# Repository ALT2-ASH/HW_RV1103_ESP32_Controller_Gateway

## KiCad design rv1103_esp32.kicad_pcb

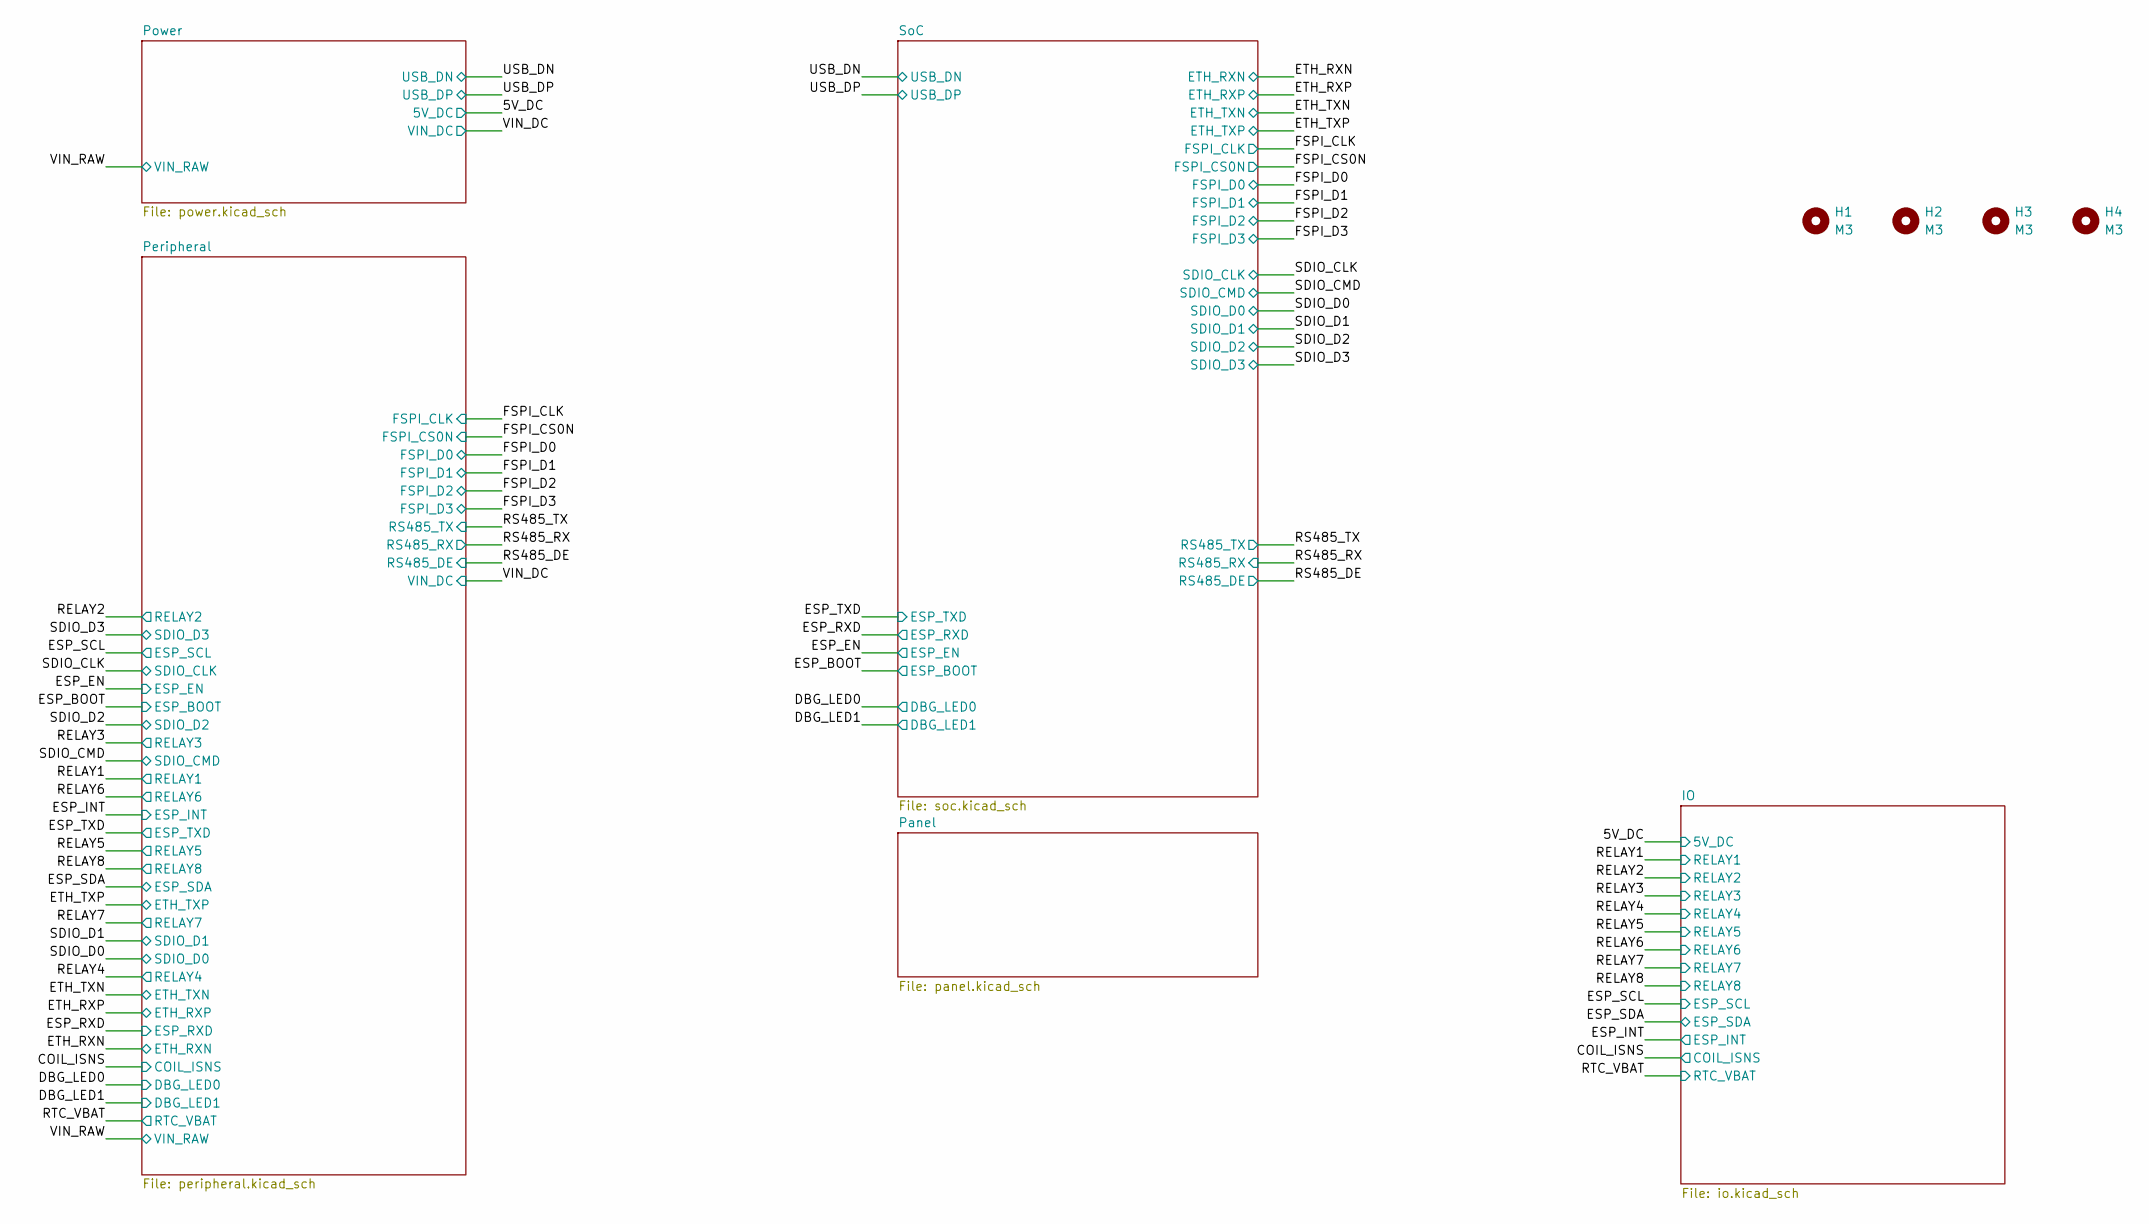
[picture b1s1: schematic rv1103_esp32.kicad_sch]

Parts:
H1, H2, H3, H4: M3; MountingHole_3.2mm_M3

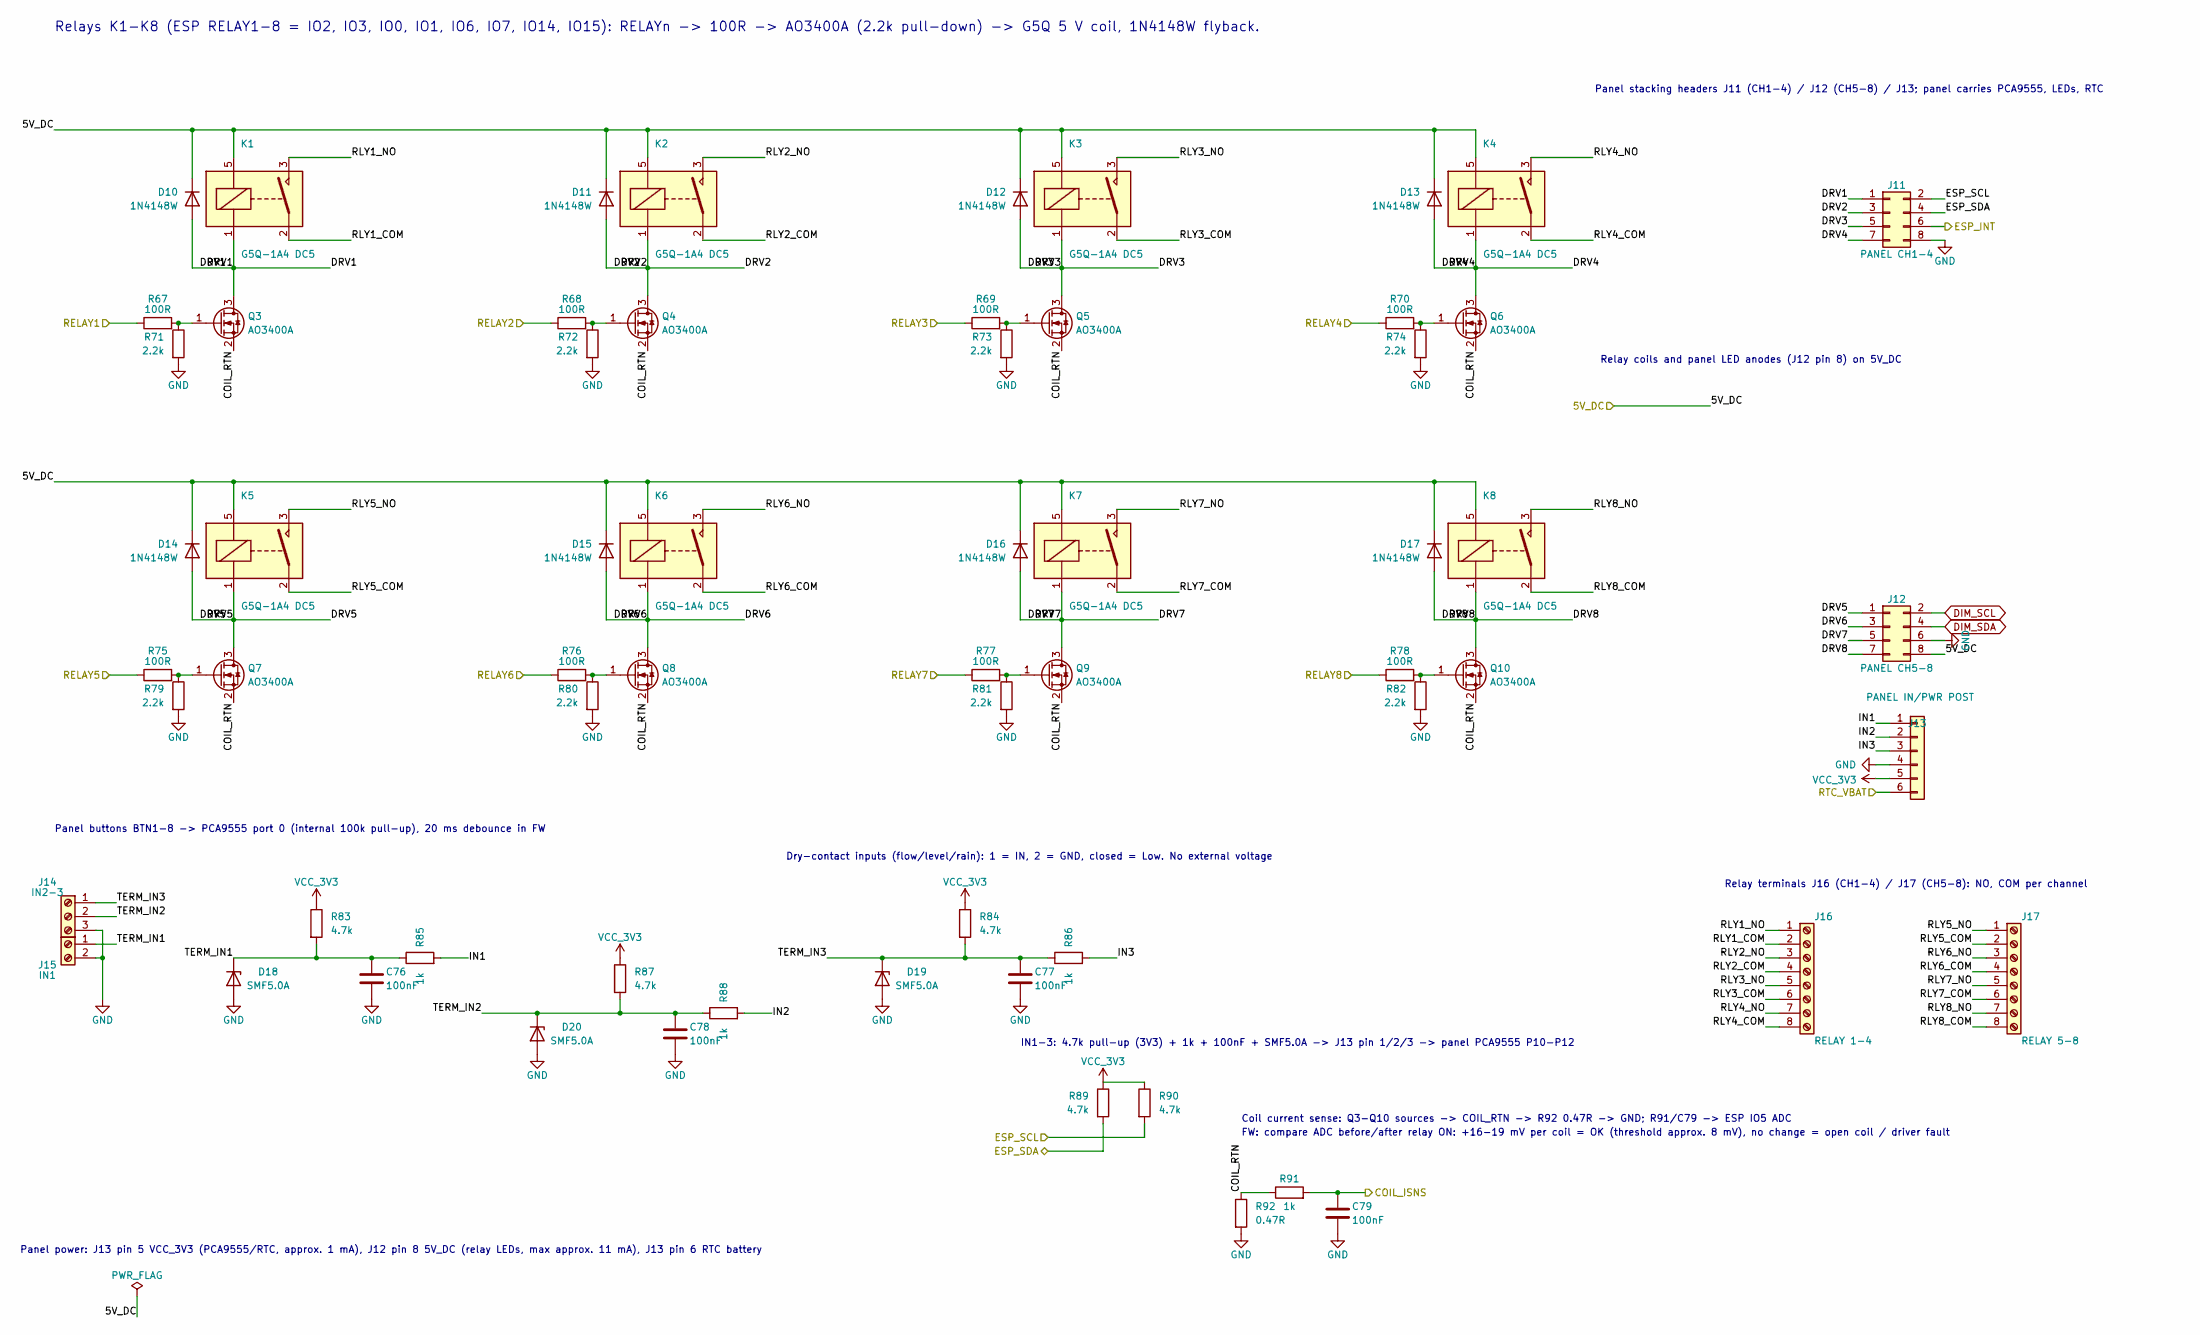
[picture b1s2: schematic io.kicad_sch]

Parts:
C76, C77, C78, C79: 100nF; C_0402_1005Metric; LCSC C1525
D10, D11, D12, D13, D14, D15, D16, D17: 1N4148W; D_SOD-123; MPN 1N4148W; LCSC C81598
D18, D19, D20: SMF5.0A; D_SOD-123F; LCSC C2759874
J11: PANEL CH1-4; PinHeader_2x04_P2.54mm_Vertical; MPN PZ254V-12-8P; LCSC C492421
J12: PANEL CH5-8; PinHeader_2x04_P2.54mm_Vertical; MPN PZ254V-12-8P; LCSC C492421
J13: PANEL IN/PWR POST; PinHeader_1x06_P2.54mm_Vertical; LCSC C492405
J14: IN2-3; TerminalBlock_DB127V-5.0_1x03_P5.00mm; MPN DB127V-5.0-3P-GN-S; LCSC C395886
J15: IN1; TerminalBlock_DB127V-5.0_1x02_P5.00mm; MPN DB127V-5.0-2P-GN-S; LCSC C395885
J16: RELAY 1-4; TerminalBlock_bornier-8_P5.08mm; MPN DB128V-5.08-8P-GN-S; LCSC C5143711
J17: RELAY 5-8; TerminalBlock_bornier-8_P5.08mm; MPN DB128V-5.08-8P-GN-S; LCSC C5143711
K1, K2, K3, K4, K5, K6, K7, K8: G5Q-1A4 DC5; Relay_SPST_Omron-G5Q-1A; MPN G5Q-1A4 DC5; LCSC_ALT C397241 G5Q-14 DC5 (SPDT 400mW coil, pa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
Q3, Q4, Q5, Q6, Q7, Q8, Q9, Q10: AO3400A; SOT-23; MPN AO3400A; LCSC C20917
R67, R68, R69, R70, R75, R76, R77, R78: 100R; R_0402_1005Metric; LCSC C25076
R71, R72, R73, R74, R79, R80, R81, R82: 2.2k; R_0402_1005Metric; LCSC C25879
R83, R84, R87, R89, R90: 4.7k; R_0402_1005Metric; LCSC C25900
R85, R86, R88, R91: 1k; R_0402_1005Metric; LCSC C11702
R92: 0.47R; R_1206_3216Metric; LCSC C327076

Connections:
/5V_DC: D10.1 (K), D11.1 (K), D12.1 (K), D13.1 (K), D14.1 (K), D15.1 (K), D16.1 (K), D17.1 (K), J12.8, K1.5, K2.5, K3.5, K4.5, K5.5, K6.5, K7.5, K8.5; also elsewhere on the board
/COIL_ISNS: C79.1, R91.2; also elsewhere on the board
/ESP_INT: J11.6; also elsewhere on the board
/ESP_SCL: J11.2, R90.2; also elsewhere on the board
/ESP_SDA: J11.4, R89.2; also elsewhere on the board
/IO/COIL_RTN: Q3.2 (S), Q4.2 (S), Q5.2 (S), Q6.2 (S), Q7.2 (S), Q8.2 (S), Q9.2 (S), Q10.2 (S), R91.1, R92.1
/IO/DRV1: D10.2 (A), J11.1, K1.1, Q3.3 (D)
/IO/DRV2: D11.2 (A), J11.3, K2.1, Q4.3 (D)
/IO/DRV3: D12.2 (A), J11.5, K3.1, Q5.3 (D)
/IO/DRV4: D13.2 (A), J11.7, K4.1, Q6.3 (D)
/IO/DRV5: D14.2 (A), J12.1, K5.1, Q7.3 (D)
/IO/DRV6: D15.2 (A), J12.3, K6.1, Q8.3 (D)
/IO/DRV7: D16.2 (A), J12.5, K7.1, Q9.3 (D)
/IO/DRV8: D17.2 (A), J12.7, K8.1, Q10.3 (D)
/IO/IN1: J13.1, R85.2
/IO/IN2: J13.2, R88.2
/IO/IN3: J13.3, R86.2
/IO/RLY1_COM: J16.2, K1.2
/IO/RLY1_NO: J16.1, K1.3
/IO/RLY2_COM: J16.4, K2.2
/IO/RLY2_NO: J16.3, K2.3
/IO/RLY3_COM: J16.6, K3.2
/IO/RLY3_NO: J16.5, K3.3
/IO/RLY4_COM: J16.8, K4.2
/IO/RLY4_NO: J16.7, K4.3
/IO/RLY5_COM: J17.2, K5.2
/IO/RLY5_NO: J17.1, K5.3
/IO/RLY6_COM: J17.4, K6.2
/IO/RLY6_NO: J17.3, K6.3
/IO/RLY7_COM: J17.6, K7.2
/IO/RLY7_NO: J17.5, K7.3
/IO/RLY8_COM: J17.8, K8.2
/IO/RLY8_NO: J17.7, K8.3
/IO/TERM_IN1: C76.1, D18.1 (K), J15.1, R83.2, R85.1
/IO/TERM_IN2: C78.1, D20.1 (K), J14.2, R87.2, R88.1
/IO/TERM_IN3: C77.1, D19.1 (K), J14.1, R84.2, R86.1
/RELAY1: R67.1; also elsewhere on the board
/RELAY2: R68.1; also elsewhere on the board
/RELAY3: R69.1; also elsewhere on the board
/RELAY4: R70.1; also elsewhere on the board
/RELAY5: R75.1; also elsewhere on the board
/RELAY6: R76.1; also elsewhere on the board
/RELAY7: R77.1; also elsewhere on the board
/RELAY8: R78.1; also elsewhere on the board
/RTC_VBAT: J13.6; also elsewhere on the board
DIM_SCL: J12.2; also elsewhere on the board
DIM_SDA: J12.4; also elsewhere on the board
GND: C76.2, C77.2, C78.2, C79.2, D18.2 (A), D19.2 (A), D20.2 (A), J11.8, J12.6, J13.4, J14.3, J15.2, R71.2, R72.2, R73.2, R74.2, R79.2, R80.2, R81.2, R82.2, R92.2; also elsewhere on the board
unnamed: Q3.1 (G), R67.2, R71.1
unnamed: Q4.1 (G), R68.2, R72.1
unnamed: Q5.1 (G), R69.2, R73.1
unnamed: Q6.1 (G), R70.2, R74.1
unnamed: Q7.1 (G), R75.2, R79.1
unnamed: Q8.1 (G), R76.2, R80.1
unnamed: Q9.1 (G), R77.2, R81.1
unnamed: Q10.1 (G), R78.2, R82.1
VCC_3V3: J13.5, R83.1, R84.1, R87.1, R89.1, R90.1; also elsewhere on the board

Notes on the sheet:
FW: compare ADC before/after relay ON: +16-19 mV per coil = OK (threshold approx. 8 mV), no change = open coil / driver fault
Relay coils and panel LED anodes (J12 pin 8) on 5V_DC
Panel stacking headers J11 (CH1-4) / J12 (CH5-8) / J13; panel carries PCA9555, LEDs, RTC
IN1-3: 4.7k pull-up (3V3) + 1k + 100nF + SMF5.0A -> J13 pin 1/2/3 -> panel PCA9555 P10-P12
Relay terminals J16 (CH1-4) / J17 (CH5-8): NO, COM per channel
Panel power: J13 pin 5 VCC_3V3 (PCA9555/RTC, approx. 1 mA), J12 pin 8 5V_DC (relay LEDs, max approx. 11 mA), J13 pin 6 RTC battery
Coil current sense: Q3-Q10 sources -> COIL_RTN -> R92 0.47R -> GND; R91/C79 -> ESP IO5 ADC
Relays K1-K8 (ESP RELAY1-8 = IO2, IO3, IO0, IO1, IO6, IO7, IO14, IO15): RELAYn -> 100R -> AO3400A (2.2k pull-down) -> G5Q 5 V coil, 1N4148W flyback.
Panel buttons BTN1-8 -> PCA9555 port 0 (internal 100k pull-up), 20 ms debounce in FW
Dry-contact inputs (flow/level/rain): 1 = IN, 2 = GND, closed = Low. No external voltage

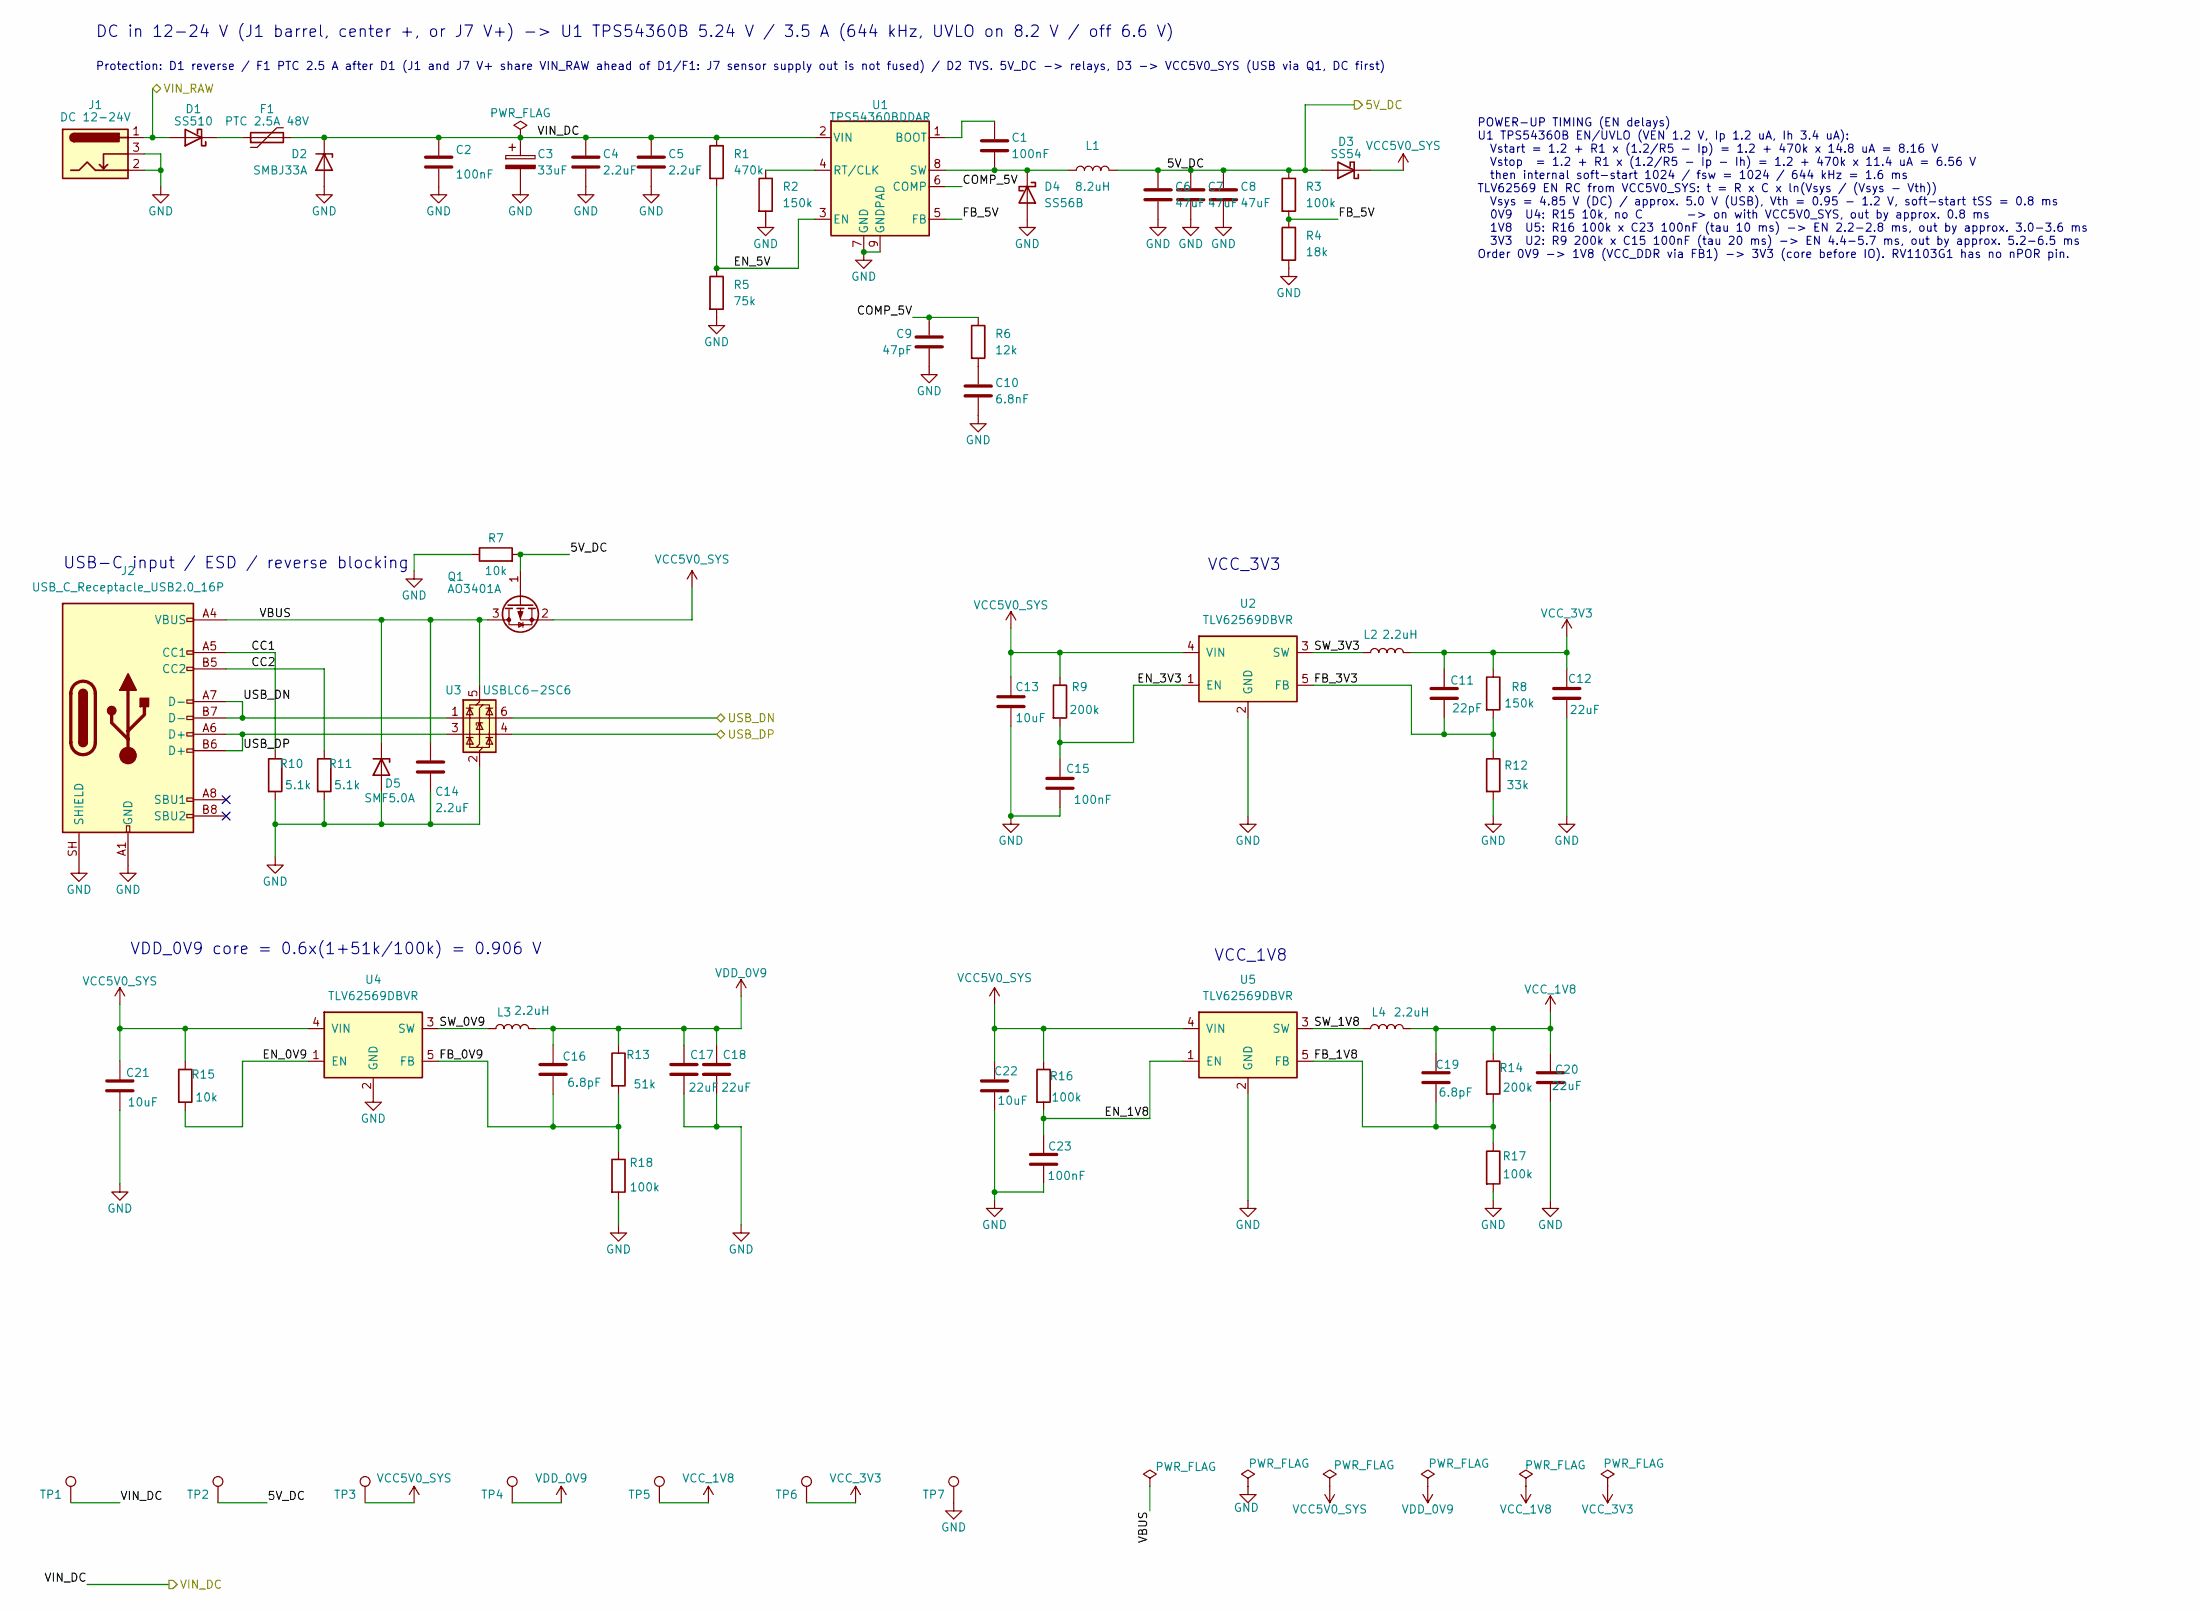
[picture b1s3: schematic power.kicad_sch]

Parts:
C1: 100nF; C_0603_1608Metric; LCSC C14663
C2: 100nF; C_0805_2012Metric; LCSC C28233
C3: 33uF; CP_Elec_6.3x7.7; Voltage 63V; MPN MV330M063E077ETR; LCSC C402500
C4, C5: 2.2uF; C_1210_3225Metric; Voltage 100V; MPN 1210B225K101NT; LCSC C42400139
C6, C7, C8: 47uF; C_1206_3216Metric; Voltage 10V; MPN CL31A476MPHNNNE; LCSC C96123
C9: 47pF; C_0402_1005Metric; MPN 0402CG470J500NT; LCSC C1567
C10: 6.8nF; C_0402_1005Metric; LCSC C1542
C11: 22pF; C_0402_1005Metric; MPN 0402CG220J500NT; LCSC C1555
C12, C17, C18, C20: 22uF; C_0603_1608Metric; LCSC C59461
C13, C21, C22: 10uF; C_0603_1608Metric; LCSC C19702
C14: 2.2uF; C_0603_1608Metric; LCSC C23630
C15, C23: 100nF; C_0402_1005Metric; LCSC C1525
C16, C19: 6.8pF; C_0402_1005Metric; LCSC C1576
D1: SS510; D_SMA; MPN SS510; LCSC C65010
D2: SMBJ33A; D_SMB; MPN SMBJ33A; LCSC C78419
D3: SS54; D_SMA; MPN SS54; LCSC C22452
D4: SS56B; D_SMB; MPN SS56B; LCSC C18199180
D5: SMF5.0A; D_SOD-123F; LCSC C2759874
F1: PTC 2.5A 48V; Fuse_2920_7451Metric; MPN 2920L250/48GR; LCSC C49326264
J1: DC 12-24V; DC-005-A200_XUNPU_Horizontal; MPN DC-005-A200; LCSC C720557
J2: USB_C_Receptacle_USB2.0_16P; USB_C_Receptacle_HRO_TYPE-C-31-D-06_Vertical; MPN TYPE-C-31-D-06A; LCSC C22464422
L1: 8.2uH; L_Sunlord_SWPA8065S; MPN FNR8065S8R2MT; LCSC C168161
L2, L3, L4: 2.2uH; L_Sunlord_SWPA4030S; MPN SWPA4030S2R2NT; LCSC C279948
Q1: AO3401A; SOT-23; MPN AO3401A; LCSC C15127
R1: 470k; R_0402_1005Metric; Tolerance 1%; MPN 0402WGF4703TCE; LCSC C25790
R2, R8: 150k; R_0402_1005Metric; Tolerance 1%; MPN 0402WGF1503TCE; LCSC C25755
R3: 100k; R_0402_1005Metric; Tolerance 1%; MPN 0402WGF1003TCE; LCSC C25741
R4: 18k; R_0402_1005Metric; Tolerance 1%; MPN 0402WGF1802TCE; LCSC C25762
R5: 75k; R_0402_1005Metric; Tolerance 1%; MPN 0402WGF7502TCE; LCSC C25798
R6: 12k; R_0402_1005Metric; Tolerance 1%; MPN 0402WGF1202TCE; LCSC C25752
R7, R15: 10k; R_0402_1005Metric; LCSC C25744
R9: 200k; R_0402_1005Metric; LCSC C25764
R10, R11: 5.1k; R_0402_1005Metric; LCSC C25905
R12: 33k; R_0402_1005Metric; Tolerance 1%; MPN 0402WGF3302TCE; LCSC C25779
R13: 51k; R_0402_1005Metric; Tolerance 1%; MPN 0402WGF5102TCE; LCSC C25794
R14: 200k; R_0402_1005Metric; Tolerance 1%; LCSC C25764
R16: 100k; R_0402_1005Metric; LCSC C25741
R17, R18: 100k; R_0402_1005Metric; Tolerance 1%; LCSC C25741
TP1: VIN_DC; TestPoint_Pad_D1.5mm
TP2: 5V_DC; TestPoint_Pad_D1.5mm
TP3: VCC5V0_SYS; TestPoint_Pad_D1.5mm
TP4: VDD_0V9; TestPoint_Pad_D1.5mm
TP5: VCC_1V8; TestPoint_Pad_D1.5mm
TP6: VCC_3V3; TestPoint_Pad_D1.5mm
TP7: GND; TestPoint_Pad_D1.5mm
U1: TPS54360BDDAR; TI_SO-PowerPAD-8_ThermalVias; MPN TPS54360BDDAR; LCSC C524806
U2, U4, U5: TLV62569DBVR; SOT-23-5_TI_DBV0005A; MPN TLV62569DBVR; LCSC C141836
U3: USBLC6-2SC6; SOT-23-6; LCSC C7519

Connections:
/5V_DC: C6.1, C7.1, C8.1, D3.2 (A), L1.2, Q1.1 (G), R3.1, R7.2, TP2.1 (1_1); also elsewhere on the board
/Power/CC1: J2.A5 (CC1), R10.1
/Power/CC2: J2.B5 (CC2), R11.1
/Power/COMP_5V: C9.1, R6.1, U1.6 (COMP)
/Power/EN_0V9: R15.2, U4.1 (EN)
/Power/EN_1V8: C23.1, R16.2, U5.1 (EN)
/Power/EN_3V3: C15.1, R9.2, U2.1 (EN)
/Power/EN_5V: R1.2, R5.1, U1.3 (EN)
/Power/FB_0V9: C16.2, R13.2, R18.1, U4.5 (FB)
/Power/FB_1V8: C19.2, R14.2, R17.1, U5.5 (FB)
/Power/FB_3V3: C11.2, R8.2, R12.1, U2.5 (FB)
/Power/FB_5V: R3.2, R4.1, U1.5 (FB)
/Power/SW_0V9: L3.1, U4.3 (SW)
/Power/SW_1V8: L4.1, U5.3 (SW)
/Power/SW_3V3: L2.1, U2.3 (SW)
/Power/VBUS: C14.1, D5.1 (K), J2.A4 (VBUS), J2.A9 (VBUS), J2.B4 (VBUS), J2.B9 (VBUS), Q1.3 (D), U3.5 (VBUS)
/USB_DN: J2.A7 (D-), J2.B7 (D-), U3.1 (I/O1), U3.6 (I/O1); also elsewhere on the board
/USB_DP: J2.A6 (D+), J2.B6 (D+), U3.3 (I/O2), U3.4 (I/O2); also elsewhere on the board
/VIN_DC: C2.1, C3.1, C4.1, C5.1, D2.1 (K), F1.2, R1.1, TP1.1 (1_1), U1.2 (VIN); also elsewhere on the board
/VIN_RAW: D1.2 (A), J1.1; also elsewhere on the board
GND: C2.2, C3.2, C4.2, C5.2, C6.2, C7.2, C8.2, C9.2, C10.2, C12.2, C13.2, C14.2, C15.2, C17.2, C18.2, C20.2, C21.2, C22.2, C23.2, D2.2 (A), D4.2 (A), D5.2 (A), J1.2, J1.3, J2.A1 (GND), J2.A12 (GND), J2.B1 (GND), J2.B12 (GND), J2.SH (SHIELD), R2.2, R4.2, R5.2, R7.1, R10.2, R11.2, R12.2, R17.2, R18.2, TP7.1 (1_1), U1.7 (GND), U1.9 (GNDPAD), U2.2 (GND), U3.2 (GND), U4.2 (GND), U5.2 (GND); also elsewhere on the board
unnamed: C10.1, R6.2
unnamed: D1.1 (K), F1.1
unnamed: C1.2, D4.1 (K), L1.1, U1.8 (SW)
unnamed: C1.1, U1.1 (BOOT)
unnamed: R2.1, U1.4 (RT/CLK)
VCC5V0_SYS: C13.1, C21.1, C22.1, D3.1 (K), Q1.2 (S), R9.1, R15.1, R16.1, TP3.1 (1_1), U2.4 (VIN), U4.4 (VIN), U5.4 (VIN)
VCC_1V8: C19.1, C20.1, L4.2, R14.1, TP5.1 (1_1); also elsewhere on the board
VCC_3V3: C11.1, C12.1, L2.2, R8.1, TP6.1 (1_1); also elsewhere on the board
VDD_0V9: C16.1, C17.1, C18.1, L3.2, R13.1, TP4.1 (1_1); also elsewhere on the board

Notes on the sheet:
VCC_3V3
DC in 12-24 V (J1 barrel, center +, or J7 V+) -> U1 TPS54360B 5.24 V / 3.5 A (644 kHz, UVLO on 8.2 V / off 6.6 V)
POWER-UP TIMING (EN delays) U1 TPS54360B EN/UVLO (VEN 1.2 V, Ip 1.2 uA, Ih 3.4 uA): Vstart = 1.2 + R1 x (1.2/R5 - Ip) = 1.2 + 470k x 14.8 uA = 8.16 V Vstop = 1.2 + R1 x (1.2/R5 - Ip - Ih) = 1.2 + 470k x 11.4 uA = 6.56 V then internal soft-start 1024 / fsw = 1024 / 644 kHz = 1.6 ms TLV62569 EN RC fr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
VDD_0V9 core = 0.6x(1+51k/100k) = 0.906 V
Protection: D1 reverse / F1 PTC 2.5 A after D1 (J1 and J7 V+ share VIN_RAW ahead of D1/F1: J7 sensor supply out is not fused) / D2 TVS. 5V_DC -> relays, D3 -> VCC5V0_SYS (USB via Q1, DC first)
VCC_1V8
USB-C input / ESD / reverse blocking

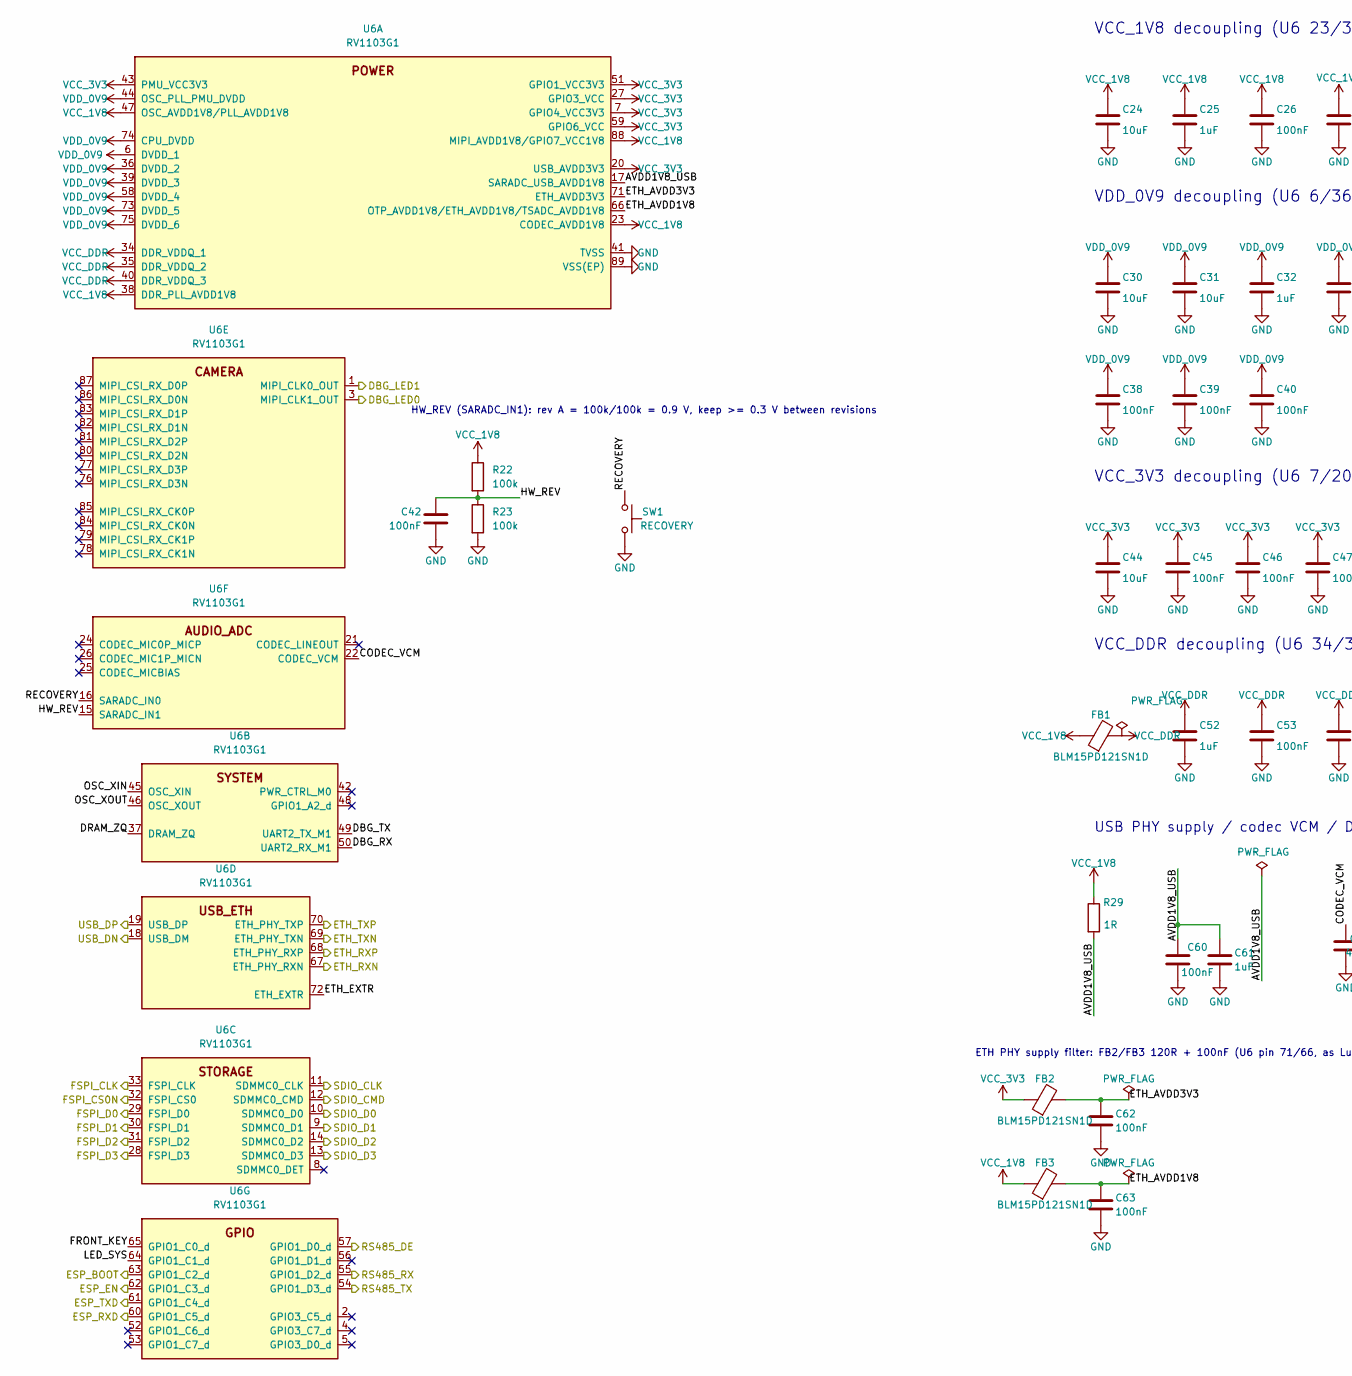
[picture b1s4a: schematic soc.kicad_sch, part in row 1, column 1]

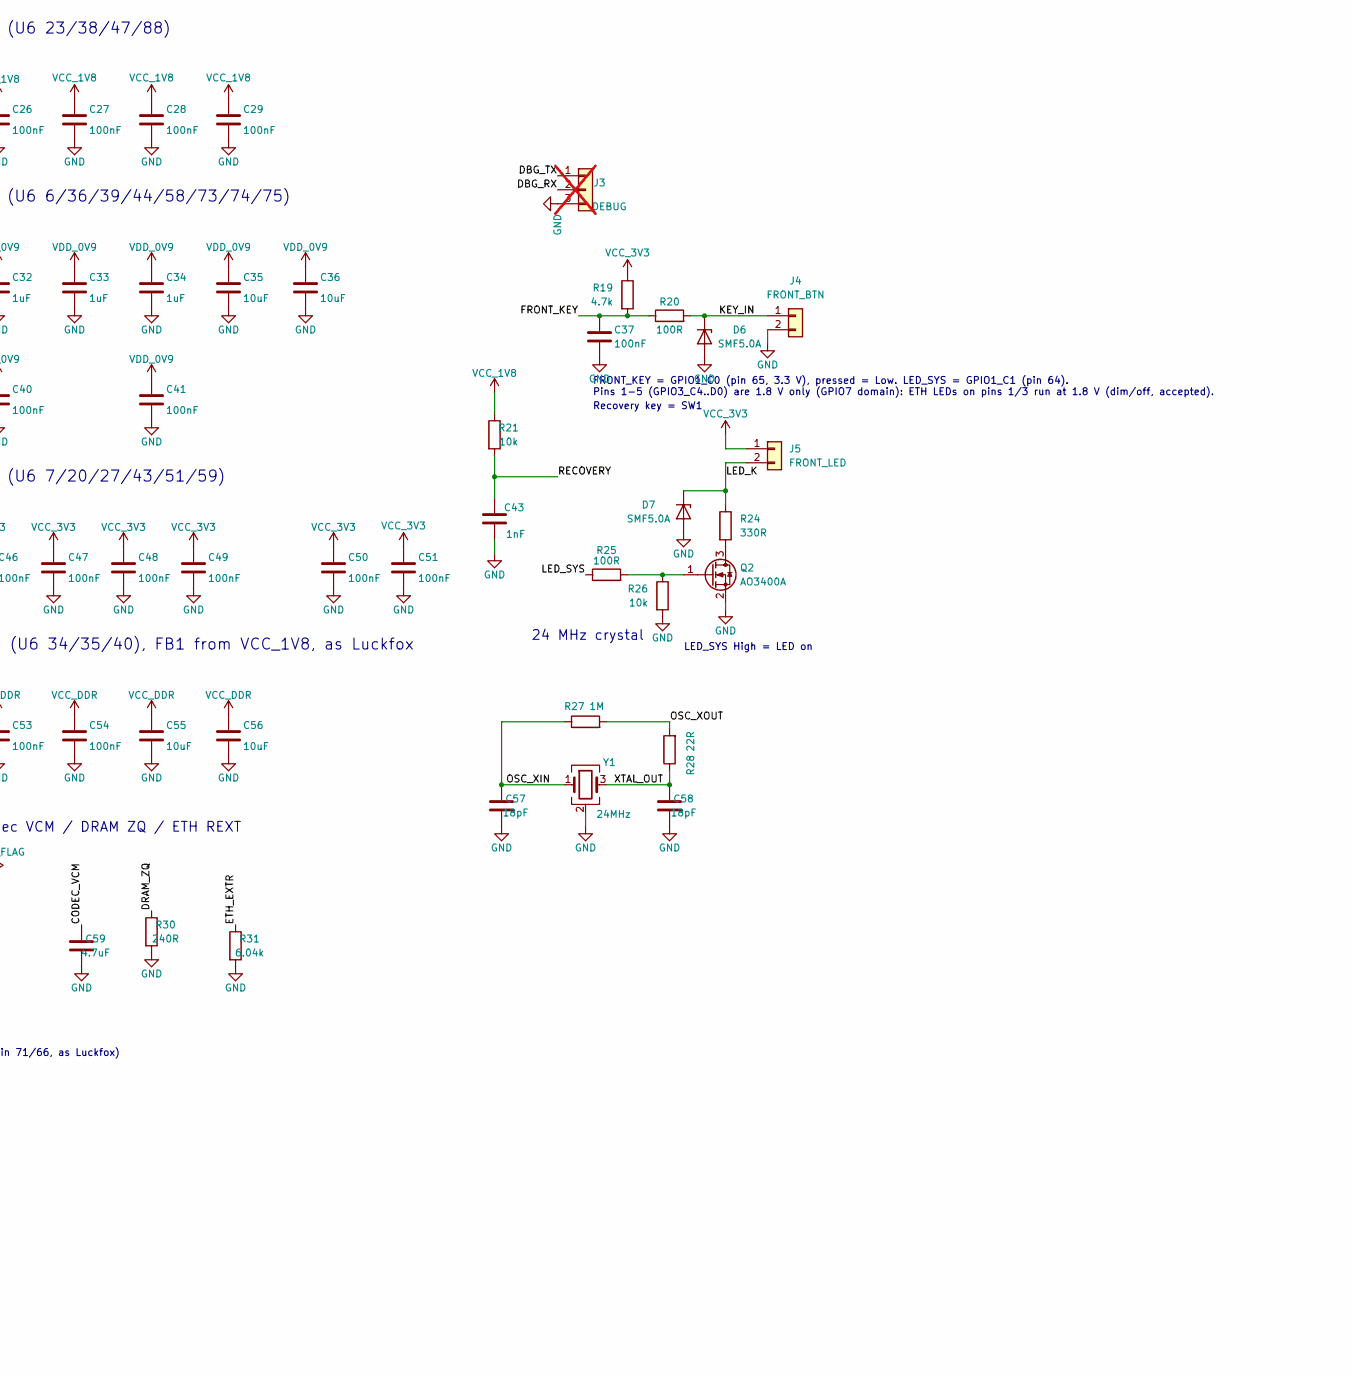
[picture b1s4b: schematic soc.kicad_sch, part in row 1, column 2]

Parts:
C24, C30, C31, C35, C36, C44, C55, C56: 10uF; C_0603_1608Metric; LCSC C19702
C25, C32, C33, C34, C52, C61: 1uF; C_0402_1005Metric; LCSC C52923
C26, C27, C28, C29, C37, C38, C39, C40, C41, C42, C45, C46, C47, C48, C49, C50, C51, C53, C54, C60, C62, C63: 100nF; C_0402_1005Metric; LCSC C1525
C43: 1nF; C_0402_1005Metric; LCSC C1523
C57, C58: 18pF; C_0402_1005Metric; LCSC C1549
C59: 4.7uF; C_0603_1608Metric; LCSC C19666
D6, D7: SMF5.0A; D_SOD-123F; LCSC C2759874
FB1, FB2, FB3: BLM15PD121SN1D; L_0402_1005Metric; LCSC C76891
J3: DEBUG; PinHeader_1x03_P2.54mm_Vertical; not fitted
J4: FRONT_BTN; PinHeader_1x02_P2.54mm_Vertical; MPN PZ254V-11-02P; LCSC C492401
J5: FRONT_LED; PinHeader_1x02_P2.54mm_Vertical; MPN PZ254V-11-02P; LCSC C492401
Q2: AO3400A; SOT-23; MPN AO3400A; LCSC C20917
R19: 4.7k; R_0402_1005Metric; LCSC C25900
R20, R25: 100R; R_0402_1005Metric; LCSC C25076
R21, R26: 10k; R_0402_1005Metric; LCSC C25744
R22, R23: 100k; R_0402_1005Metric; LCSC C25741
R24: 330R; R_0402_1005Metric; LCSC C25104
R27: 1M; R_0402_1005Metric; LCSC C26083
R28: 22R; R_0402_1005Metric; LCSC C25092
R29: 1R; R_0402_1005Metric; MPN RC0402FR-071RL; LCSC C25086
R30: 240R; R_0402_1005Metric; Tolerance 1%; MPN RC0402FR-07240RL; LCSC C114755
R31: 6.04k; R_0402_1005Metric; Tolerance 1%; MPN RC0402FR-076K04L; LCSC C97819
SW1: RECOVERY; SW_SPST_TL3342; MPN TS-1187A-B-A-B; LCSC C318884
U6: RV1103G1; QFN-88-1EP_9x9mm_P0.35mm_EP6.5x6.5mm; MPN RV1103G1; LCSC C5307358
Y1: 24MHz; Crystal_SMD_2016-4Pin_2.0x1.6mm; LCSC C5261099

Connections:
/DBG_LED0: U6.3 (MIPI_CLK1_OUT); also elsewhere on the board
/DBG_LED1: U6.1 (MIPI_CLK0_OUT); also elsewhere on the board
/ESP_BOOT: U6.63 (GPIO1_C2_d); also elsewhere on the board
/ESP_EN: U6.62 (GPIO1_C3_d); also elsewhere on the board
/ESP_RXD: U6.60 (GPIO1_C5_d); also elsewhere on the board
/ESP_TXD: U6.61 (GPIO1_C4_d); also elsewhere on the board
/ETH_RXN: U6.67 (ETH_PHY_RXN); also elsewhere on the board
/ETH_RXP: U6.68 (ETH_PHY_RXP); also elsewhere on the board
/ETH_TXN: U6.69 (ETH_PHY_TXN); also elsewhere on the board
/ETH_TXP: U6.70 (ETH_PHY_TXP); also elsewhere on the board
/FSPI_CLK: U6.33 (FSPI_CLK); also elsewhere on the board
/FSPI_CS0N: U6.32 (FSPI_CS0); also elsewhere on the board
/FSPI_D0: U6.29 (FSPI_D0); also elsewhere on the board
/FSPI_D1: U6.30 (FSPI_D1); also elsewhere on the board
/FSPI_D2: U6.31 (FSPI_D2); also elsewhere on the board
/FSPI_D3: U6.28 (FSPI_D3); also elsewhere on the board
/RS485_DE: U6.57 (GPIO1_D0_d); also elsewhere on the board
/RS485_RX: U6.55 (GPIO1_D2_d); also elsewhere on the board
/RS485_TX: U6.54 (GPIO1_D3_d); also elsewhere on the board
/SDIO_CLK: U6.11 (SDMMC0_CLK); also elsewhere on the board
/SDIO_CMD: U6.12 (SDMMC0_CMD); also elsewhere on the board
/SDIO_D0: U6.10 (SDMMC0_D0); also elsewhere on the board
/SDIO_D1: U6.9 (SDMMC0_D1); also elsewhere on the board
/SDIO_D2: U6.14 (SDMMC0_D2); also elsewhere on the board
/SDIO_D3: U6.13 (SDMMC0_D3); also elsewhere on the board
/SoC/AVDD1V8_USB: C60.1, C61.1, R29.2, U6.17 (SARADC_USB_AVDD1V8)
/SoC/CODEC_VCM: C59.1, U6.22 (CODEC_VCM)
/SoC/DBG_RX: J3.2, U6.50 (UART2_RX_M1)
/SoC/DBG_TX: J3.1, U6.49 (UART2_TX_M1)
/SoC/DRAM_ZQ: R30.1, U6.37 (DRAM_ZQ)
/SoC/ETH_AVDD1V8: C63.1, FB3.2, U6.66 (OTP_AVDD1V8/ETH_AVDD1V8/TSADC_AVDD1V8)
/SoC/ETH_AVDD3V3: C62.1, FB2.2, U6.71 (ETH_AVDD3V3)
/SoC/ETH_EXTR: R31.1, U6.72 (ETH_EXTR)
/SoC/FRONT_KEY: C37.1, R19.2, R20.1, U6.65 (GPIO1_C0_d)
/SoC/HW_REV: C42.1, R22.2, R23.1, U6.15 (SARADC_IN1)
/SoC/KEY_IN: D6.1 (K), J4.1, R20.2
/SoC/LED_K: D7.1 (K), J5.2, R24.1
/SoC/LED_SYS: R25.1, U6.64 (GPIO1_C1_d)
/SoC/OSC_XIN: C57.1, R27.1, U6.45 (OSC_XIN), Y1.1
/SoC/OSC_XOUT: R27.2, R28.2, U6.46 (OSC_XOUT)
/SoC/RECOVERY: C43.1, R21.2, SW1.1, U6.16 (SARADC_IN0)
/SoC/XTAL_OUT: C58.1, R28.1, Y1.3
/USB_DN: U6.18 (USB_DM); also elsewhere on the board
/USB_DP: U6.19 (USB_DP); also elsewhere on the board
GND: C24.2, C25.2, C26.2, C27.2, C28.2, C29.2, C30.2, C31.2, C32.2, C33.2, C34.2, C35.2, C36.2, C37.2, C38.2, C39.2, C40.2, C41.2, C42.2, C43.2, C44.2, C45.2, C46.2, C47.2, C48.2, C49.2, C50.2, C51.2, C52.2, C53.2, C54.2, C55.2, C56.2, C57.2, C58.2, C59.2, C60.2, C61.2, C62.2, C63.2, D6.2 (A), D7.2 (A), J3.3, J4.2, Q2.2 (S), R23.2, R26.2, R30.2, R31.2, SW1.2, U6.41 (TVSS), U6.89 (VSS(EP)), Y1.2 (G), Y1.4 (G); also elsewhere on the board
unnamed: Q2.3 (D), R24.2
unnamed: Q2.1 (G), R25.2, R26.1
VCC_1V8: C24.1, C25.1, C26.1, C27.1, C28.1, C29.1, FB1.1, FB3.1, R21.1, R22.1, R29.1, U6.23 (CODEC_AVDD1V8), U6.38 (DDR_PLL_AVDD1V8), U6.47 (OSC_AVDD1V8/PLL_AVDD1V8), U6.88 (MIPI_AVDD1V8/GPIO7_VCC1V8); also elsewhere on the board
VCC_3V3: C44.1, C45.1, C46.1, C47.1, C48.1, C49.1, C50.1, C51.1, FB2.1, J5.1, R19.1, U6.7 (GPIO4_VCC3V3), U6.20 (USB_AVDD3V3), U6.27 (GPIO3_VCC), U6.43 (PMU_VCC3V3), U6.51 (GPIO1_VCC3V3), U6.59 (GPIO6_VCC); also elsewhere on the board
VCC_DDR: C52.1, C53.1, C54.1, C55.1, C56.1, FB1.2, U6.34 (DDR_VDDQ_1), U6.35 (DDR_VDDQ_2), U6.40 (DDR_VDDQ_3)
VDD_0V9: C30.1, C31.1, C32.1, C33.1, C34.1, C35.1, C36.1, C38.1, C39.1, C40.1, C41.1, U6.6 (DVDD_1), U6.36 (DVDD_2), U6.39 (DVDD_3), U6.44 (OSC_PLL_PMU_DVDD), U6.58 (DVDD_4), U6.73 (DVDD_5), U6.74 (CPU_DVDD), U6.75 (DVDD_6); also elsewhere on the board

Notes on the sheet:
ETH PHY supply filter: FB2/FB3 120R + 100nF (U6 pin 71/66, as Luckfox)
VDD_0V9 decoupling (U6 6/36/39/44/58/73/74/75)
Recovery key = SW1
VCC_3V3 decoupling (U6 7/20/27/43/51/59)
LED_SYS High = LED on
HW_REV (SARADC_IN1): rev A = 100k/100k = 0.9 V, keep >= 0.3 V between revisions
VCC_1V8 decoupling (U6 23/38/47/88)
FRONT_KEY = GPIO1_C0 (pin 65, 3.3 V), pressed = Low. LED_SYS = GPIO1_C1 (pin 64). Pins 1-5 (GPIO3_C4..D0) are 1.8 V only (GPIO7 domain): ETH LEDs on pins 1/3 run at 1.8 V (dim/off, accepted).
USB PHY supply / codec VCM / DRAM ZQ / ETH REXT
VCC_DDR decoupling (U6 34/35/40), FB1 from VCC_1V8, as Luckfox
24 MHz crystal
